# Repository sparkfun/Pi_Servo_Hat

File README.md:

SparkFun Pi Servo pHAT
=====================

[SparkFun Servo pHAT for Raspberry Pi (DEV-15316)](https://www.sparkfun.com/products/15316)

<!--
<table class="table table-hover table-striped table-bordered">
  <tr align="center">
   <td></td>
   <td></td>
  </tr>
  <tr align="center">
    <td><i>Pi Servo Hat [<a href="https://www.sparkfun.com/products/14328">DEV-14328</a>]</i></td>
    <td><i>SparkFun Raspberry Pi Zero W Camera Kit [<a href="https://www.sparkfun.com/products/14329">KIT-14329</a>]</i></td>
  </tr>
</table>
-->

The Pi Servo pHAT is a hat that adds, via I<sup>2</sup>C, the ability to control up to 16 servo motors with a Raspberry Pi. It is the same size and form factor as a Pi Zero or Pi Zero W. The Pi Servo pHAT is great for adding pan/tilt control with the Raspberry Pi Camera to create homemade motion-activated security systems, webcam interfaces for streaming, or monitoring stations for any number of projects and adventures. 

Repository Contents
-------------------
* **/Hardware** - All Eagle design files (.brd, .sch)
* **/Examples** - All Python examples for this board
* **/Production** - Test bed files and production panel files

Documentation
--------------
* **[Hookup Guide](https://learn.sparkfun.com/tutorials/pi-servo-phat-v2-hookup-guide)** - Basic hookup guide for the Pi Servo pHAT.
* **[Setting Up the Pi Zero Wireless Pan-Tilt Camera](https://learn.sparkfun.com/tutorials/setting-up-the-pi-zero-wireless-pan-tilt-camera)** - Pi Zero Wireless Pan-Tilt Camera Kit Assembly Guide (*can be used with the Pi Servo pHAT*). 

Product Versions
--------------
* [SparkFun Pi Servo HAT (DEV-14328)](https://www.sparkfun.com/products/14328) - Original product release.
* [SparkFun Pi Servo pHAT for Raspberry Pi (DEV-15316)](https://www.sparkfun.com/products/15316)- Updated USB-to-serial converter (CH340C) and USB-C connector, corrected to Pi HAT form factor, added QWiic connector and reverse current protection, provides 4-pin header for compatibility with Sphero RVR, and comes with pre-soldered female 40-pin GPIO header.

License Information
-------------------

This product is _**open source**_! 

Please review the LICENSE.md file for license information. 

If you have any questions or concerns on licensing, please visit the [SparkFun Forum](https://forum.sparkfun.com/index.php) and post a topic. <!--For more general questions related to our Raspberry Pi hats, please visit this section of the forum: [SparkFun Forums: Raspberry Pi Products](https://forum.sparkfun.com/viewforum.php?f=105)-->

Distributed as-is; no warranty is given.

- Your friends at SparkFun.

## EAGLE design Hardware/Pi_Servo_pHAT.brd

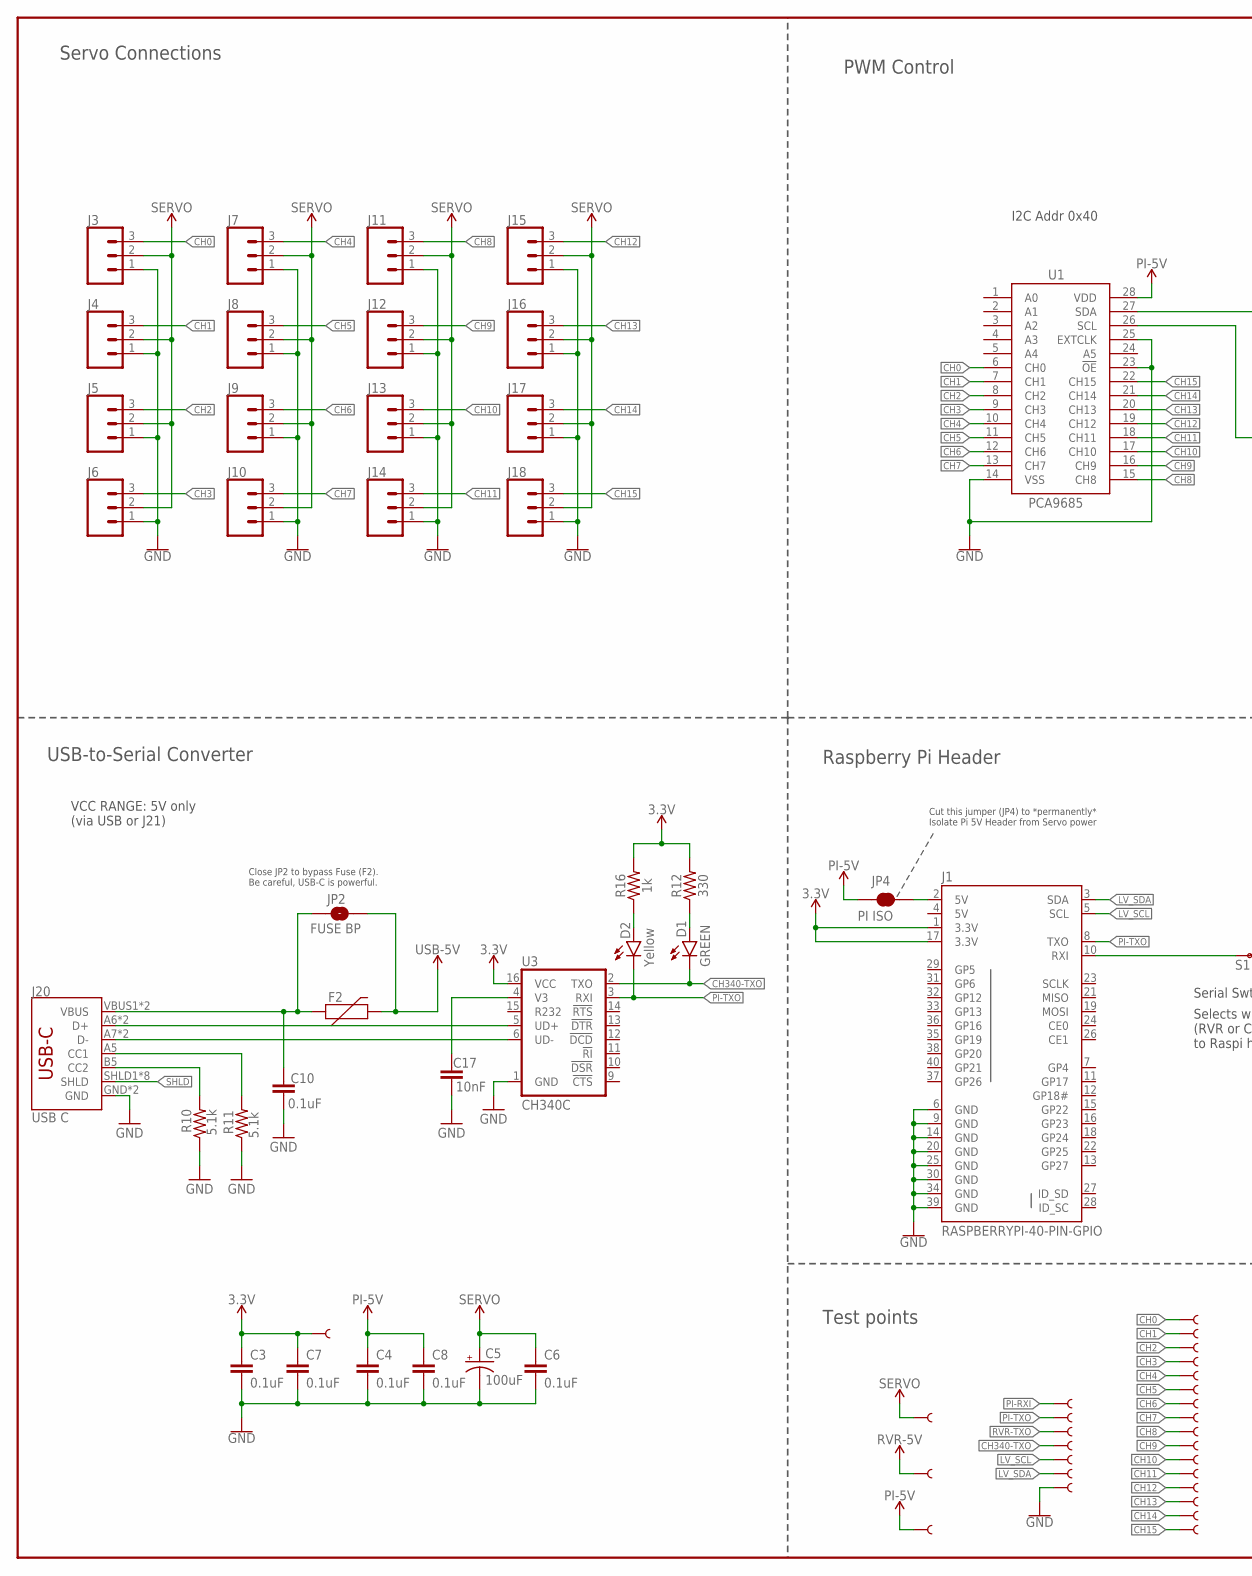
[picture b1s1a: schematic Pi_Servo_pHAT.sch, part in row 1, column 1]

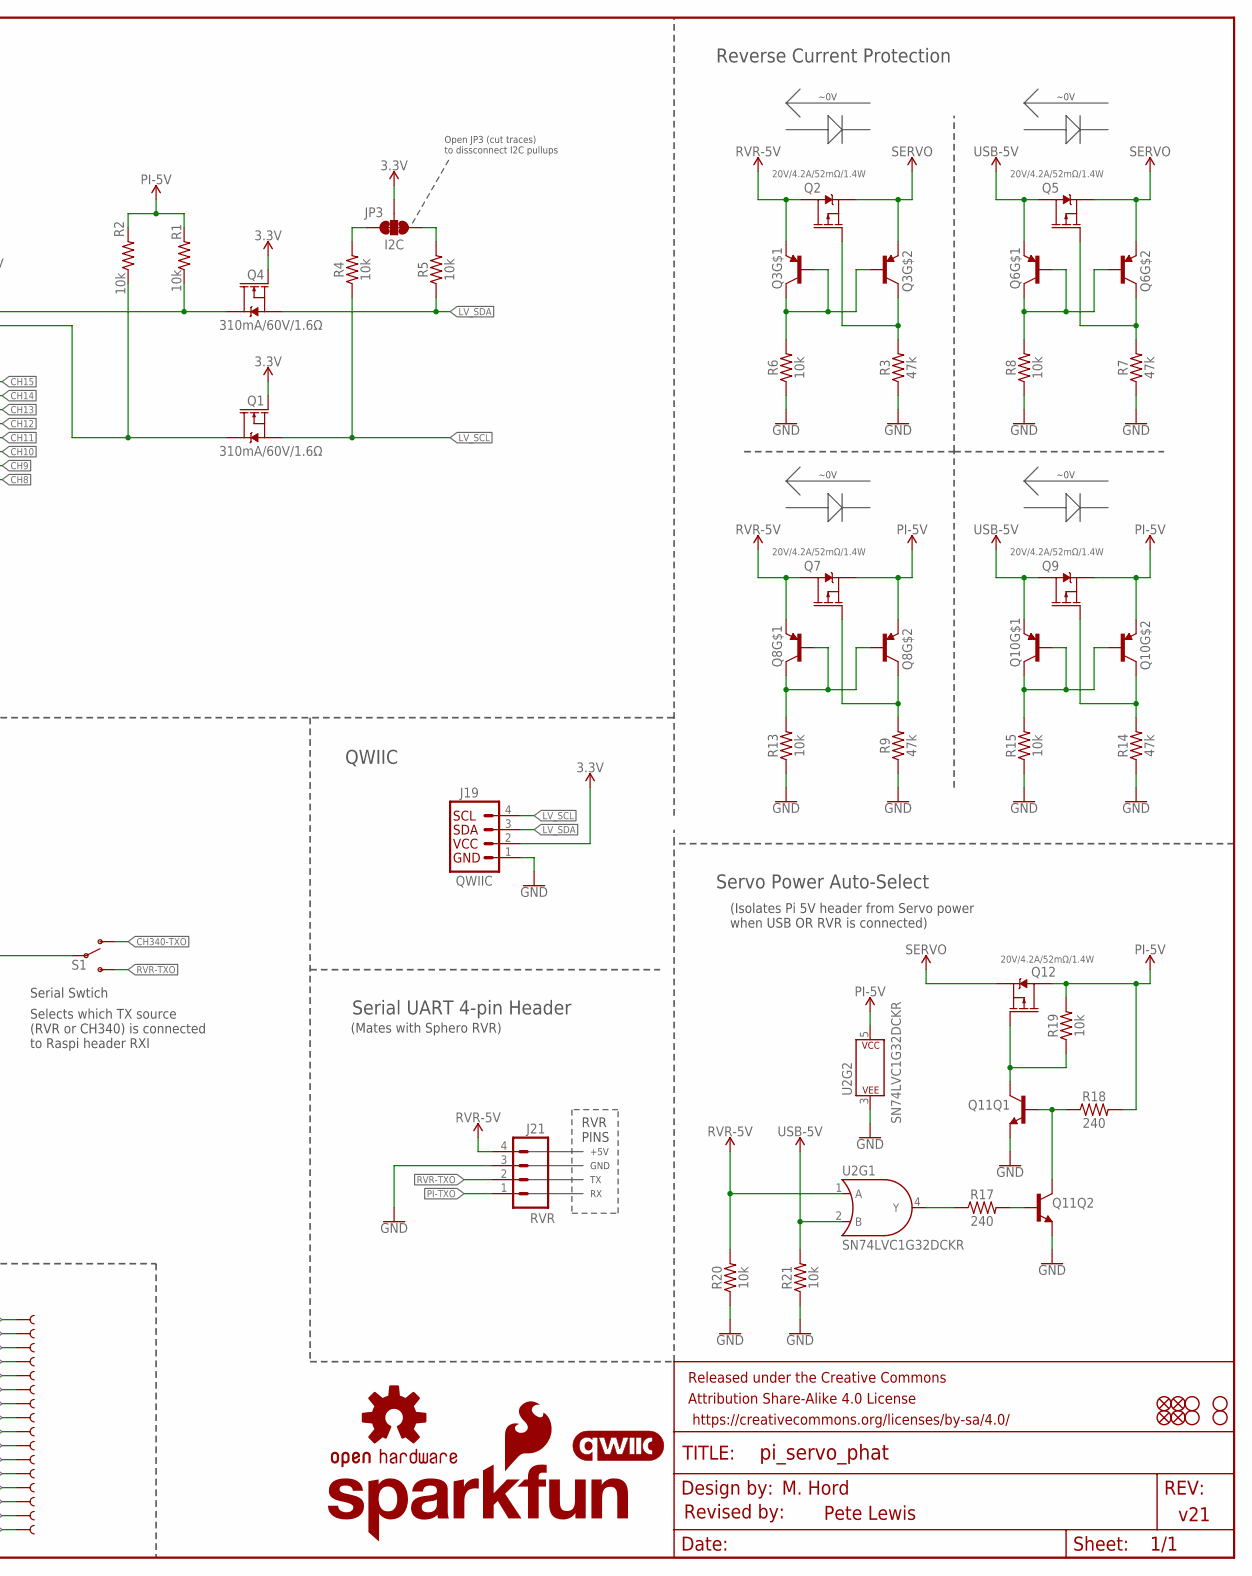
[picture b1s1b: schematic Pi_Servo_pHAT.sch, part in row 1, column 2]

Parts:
C3, C4, C6, C7, C8, C10: 0.1uF; 0603
C5: 100uF; PANASONIC_D
C17: 10nF; 0603
D1: GREEN; LED-0603
D2: Yellow; LED-0603
F2: 16V/2.5A(5A TRIP); 1812
FD1, FD2, FD3, FD4: FIDUCIALUFIDUCIAL; FIDUCIAL-MICRO
FRAME2: FRAME-LEDGER; CREATIVE_COMMONS
H1, H2, H3, H4: STAND-OFF
J1: RASPBERRYPI-40-PIN-GPIO; 2X20
J3, J4, J5, J6, J7, J8, J9, J10, J11, J12, J13, J14, J15, J16, J17, J18: CONN_03; 1X03
J19: QWIIC; JST04_1MM_RA
J20: USB C; USB-C-16P
J21: RVR; 1X04_LOCK
JP2: FUSE BP; SMT-JUMPER_2_NO_SILK
JP3: I2C; SMT-JUMPER_3_2-NC_TRACE_SILK
JP4: PI ISO; SMT-JUMPER_2_NC_TRACE_SILK
LOGO1: SFE_LOGO_NAME_FLAME.1_INCH; SFE_LOGO_NAME_FLAME_.1
LOGO2: OSHW-LOGOS; OSHW-LOGO-S
Q1, Q4: 310mA/60V/1.6Ω; SOT323
Q2, Q5, Q7, Q9, Q12: 20V/4.2A/52mΩ/1.4W; SOT23-3
Q3, Q6, Q8, Q10: TRANS_PNP_DUALSOT-363; SOT363_PHILIPS
Q11: TRANS_NPN_DUAL-MBT3904DW1T1; SC70-6
R1, R2, R4, R5, R6, R8, R13, R15, R19, R20, R21: 10k; 0603
R3, R7, R9, R14: 47k; 0603
R10, R11: 5.1k; 0603
R12: 330; 0603
R16: 1k; 0603
R17, R18: 240; 0603
S1: SWITCH-SPDT-SMD-RIGHT-ANGLE; SWITCH_SPST_SMD_A
TP0, TP1, TP2, TP3, TP4, TP5, TP6, TP7, TP8, TP9, TP10, TP11, TP12, TP13, TP14, TP15, TP16, TP17, TP20, TP21, TP22, TP23, TP24, TP25, TP26: TEST-POINT3X4; PAD.03X.04
TP18, TP19: TEST-POINTTP_15TH_THRU; TP_15TH
U1: PCA9685; TSSOP-28_4MM
U2: SN74LVC1G32DCKR; SOT353
U3: CH340C; SO016
U$1: QWIIC_LOGO_5MM; QWIIC_5MM

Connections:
3.3V: C3.1, C7.1, J1.1 (3.3V), J1.17 (3.3V), J19.2, JP3.2, Q1.1 (G), Q4.1 (G), R12.2, R16.2, TP22.P$1, U3.16 (VCC)
5V: J1.4 (5V)
CC1: J20.A5 (CC1), R11.2
CC2: J20.B5 (CC2), R10.2
CH0: J3.3, TP0.P$1, U1.6 (CH0)
CH1: J4.3, TP1.P$1, U1.7 (CH1)
CH2: J5.3, TP2.P$1, U1.8 (CH2)
CH3: J6.3, TP3.P$1, U1.9 (CH3)
CH4: J7.3, TP4.P$1, U1.10 (CH4)
CH5: J8.3, TP5.P$1, U1.11 (CH5)
CH6: J9.3, TP6.P$1, U1.12 (CH6)
CH7: J10.3, TP7.P$1, U1.13 (CH7)
CH8: J11.3, TP8.P$1, U1.15 (CH8)
CH9: J12.3, TP9.P$1, U1.16 (CH9)
CH10: J13.3, TP10.P$1, U1.17 (CH10)
CH11: J14.3, TP11.P$1, U1.18 (CH11)
CH12: J15.3, TP12.P$1, U1.19 (CH12)
CH13: J16.3, TP13.P$1, U1.20 (CH13)
CH14: J17.3, TP14.P$1, U1.21 (CH14)
CH15: J18.3, TP15.P$1, U1.22 (CH15)
CH340-TXO: D1.C, S1.1 (O), TP23.P$1, U3.2 (TXO)
D+: J20.A6 (D+), J20.B6 (D+), U3.5 (UD+)
D-: J20.A7 (D-), J20.B7 (D-), U3.6 (UD-)
GND: C3.2, C4.2, C5.-, C6.2, C7.2, C8.2, C10.2, C17.2, J1.6 (GND), J1.9 (GND), J1.14 (GND), J1.20 (GND), J1.25 (GND), J1.30 (GND), J1.34 (GND), J1.39 (GND), J3.1, J4.1, J5.1, J6.1, J7.1, J8.1, J9.1, J10.1, J11.1, J12.1, J13.1, J14.1, J15.1, J16.1, J17.1, J18.1, J19.1, J20.GND, J20.GND2 (GND), J21.3, Q11.1 (E), Q11.4 (E), R3.1, R6.1, R7.1, R8.1, R9.1, R10.1, R11.1, R13.1, R14.1, R15.1, R20.1, R21.1, TP17.P$1, U1.14 (VSS), U1.23 (!OE), U1.25 (EXTCLK), U2.3 (P$V-), U3.1 (GND)
LV_SCL: J1.5 (SCL), J19.4, Q1.2 (S), R4.1, TP18.P$1
LV_SDA: J1.3 (SDA), J19.3, Q4.2 (S), R5.1, TP19.P$1
unnamed: Q5.1 (G), Q6.3 (C), R7.2
unnamed: JP3.3, R4.2
unnamed: Q1.3 (D), R2.1, U1.26 (SCL)
unnamed: Q4.3 (D), R1.1, U1.27 (SDA)
unnamed: JP3.1, R5.2
unnamed: D2.A, R16.1
unnamed: D1.A, R12.1
unnamed: Q11.2 (B), R17.2
unnamed: Q2.1 (G), Q3.3 (C), R3.2
unnamed: Q3.2 (B), Q3.5 (B), Q3.6 (C), R6.2
unnamed: Q6.2 (B), Q6.5 (B), Q6.6 (C), R8.2
unnamed: Q11.5 (B), Q11.6 (C), R18.1
unnamed: Q11.3 (C), Q12.1 (G), R19.1
unnamed: C17.1, U3.4 (V3)
unnamed: Q7.1 (G), Q8.3 (C), R9.2
unnamed: Q8.2 (B), Q8.5 (B), Q8.6 (C), R13.2
unnamed: R17.1, U2.4 (Y)
unnamed: Q9.1 (G), Q10.3 (C), R14.2
unnamed: Q10.2 (B), Q10.5 (B), Q10.6 (C), R15.2
unnamed: J1.2 (5V), JP4.2
PI-5V: C4.1, C8.1, JP4.1, Q7.2 (S), Q8.4 (E), Q9.2 (S), Q10.4 (E), Q12.3 (D), R1.2, R2.2, R18.2, R19.2, TP24.P$1, U1.28 (VDD), U2.5 (P$V+)
PI-RXI: J1.10 (RXI), S1.2, TP26.P$1
PI-TXO: D2.C, J1.8 (TXO), J21.1, TP20.P$1, U3.3 (RXI)
RVR-5V: J21.4, Q2.3 (D), Q3.1 (E), Q7.3 (D), Q8.1 (E), R20.2, TP25.P$1, U2.1 (A)
RVR-TXO: J21.2, S1.3 (S), TP21.P$1
SERVO: C5.+, C6.1, J3.2, J4.2, J5.2, J6.2, J7.2, J8.2, J9.2, J10.2, J11.2, J12.2, J13.2, J14.2, J15.2, J16.2, J17.2, J18.2, Q2.2 (S), Q3.4 (E), Q5.2 (S), Q6.4 (E), Q12.2 (S), TP16.P$1
SHLD: J20.SHLD1 (SHLD), J20.SHLD2 (SHLD), J20.SHLD3 (SHLD), J20.SHLD4 (SHLD), J20.SHLD5 (SHLD), J20.SHLD6 (SHLD), J20.SHLD7 (SHLD), J20.SHLD8 (SHLD)
USB-5V: F2.2, JP2.2, Q5.3 (D), Q6.1 (E), Q9.3 (D), Q10.1 (E), R21.2, U2.2 (B)
VBUS: C10.1, F2.1, J20.VBUS1 (VBUS), J20.VBUS2 (VBUS), JP2.1

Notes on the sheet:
M. Hord
v21
Raspberry Pi Header
PWM Control
Servo Connections
Cut this jumper (JP4) to *permanently* Isolate Pi 5V Header from Servo power
I2C Addr 0x40
Revised by:
Pete Lewis
USB-to-Serial Converter
Close JP2 to bypass Fuse (F2). Be careful, USB-C is powerful.
Serial UART 4-pin Header
(Mates with Sphero RVR)
Open JP3 (cut traces) to dissconnect I2C pullups
VCC RANGE: 5V only (via USB or J21)
~0V
Serial Swtich
Selects which TX source (RVR or CH340) is connected to Raspi header RXI
QWIIC
Servo Power Auto-Select
Reverse Current Protection
(Isolates Pi 5V header from Servo power when USB OR RVR is connected)
Test points
RVR PINS
+5V
GND

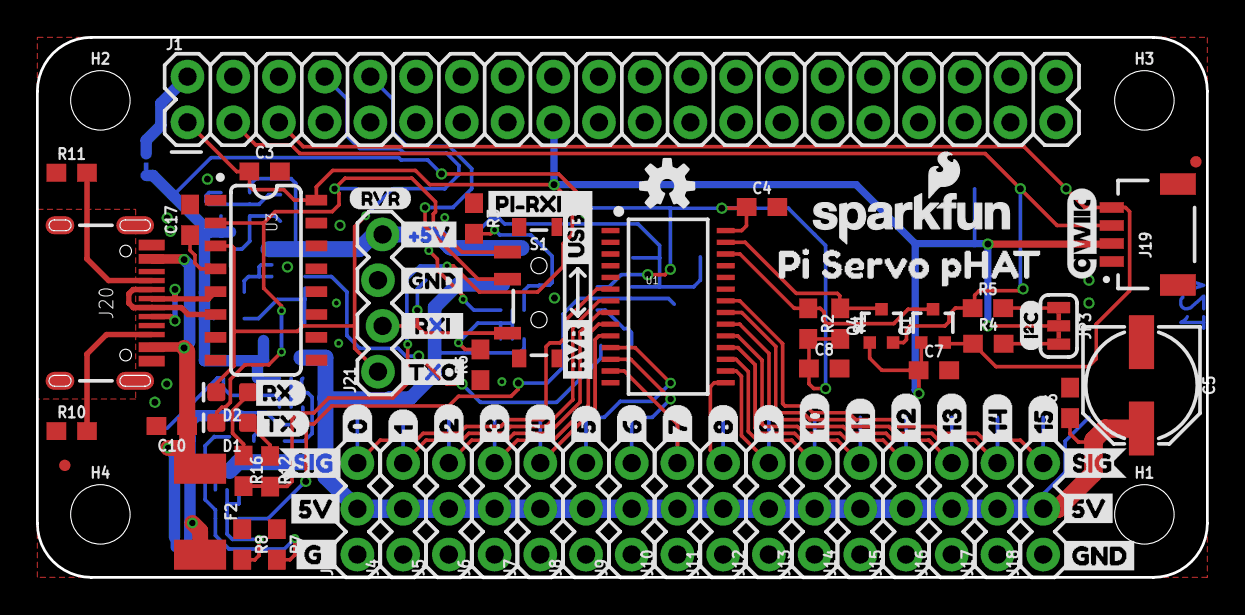
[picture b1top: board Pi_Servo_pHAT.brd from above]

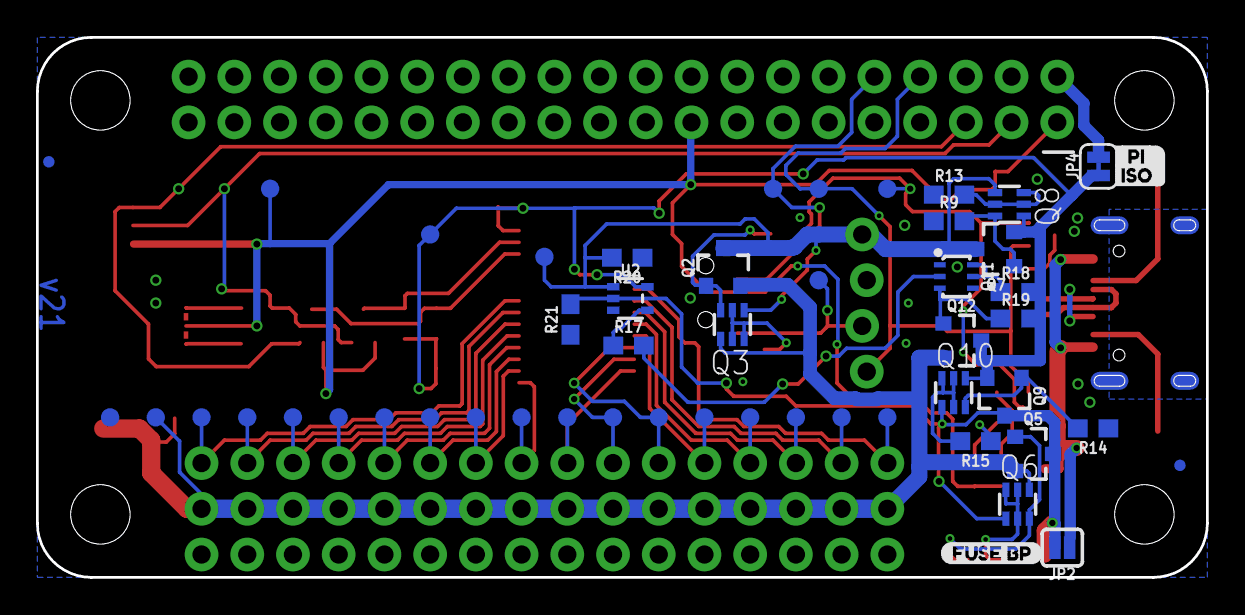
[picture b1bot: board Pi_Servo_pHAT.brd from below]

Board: 2 copper layers, 65.0 x 30.0 mm, 148 parts (52 on the bottom side), 54 nets.

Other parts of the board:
U$2: I_SUPER2_C-()-03
U$3: 028
U$4: 129
U$5: 230
U$6: 331
U$7: 432
U$8: 533
U$9: 634
U$10: 735
U$11: 836
U$12: 937
U$13: 1038
U$14: 1139
U$15: 1240
U$16: 1341
U$17: 1442
U$18: 1543
U$20, U$24: 5V5
U$21: SIG2
U$22: SIG3
U$23: GND25
U$25: TXO0
U$26: PI#RXI2
U$27: #5V3
U$28: GND2
U$30: RASP_μPI_HAT_SPECIFICATION
U$31: RVR1
U$32: ISO1
U$33: _RXI_0
U$34: USB0
U$35: PI0
U$36: RX0
U$37: TX1
U$38: RVR0
U$39: FUSE_BP0
U$40: G_0
U$41: PI_SERVO_PHAT0

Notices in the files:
parts and their libraries:
SparkFun-Capacitors: Licensing: Creative Commons ShareAlike 4.0 International - https://creativecommons.org/licenses/by-sa/4.0
SparkFun-Aesthetics: Released under the Creative Commons Attribution Share-Alike 4.0 License
SparkFun-Aesthetics: https://creativecommons.org/licenses/by-sa/4.0
